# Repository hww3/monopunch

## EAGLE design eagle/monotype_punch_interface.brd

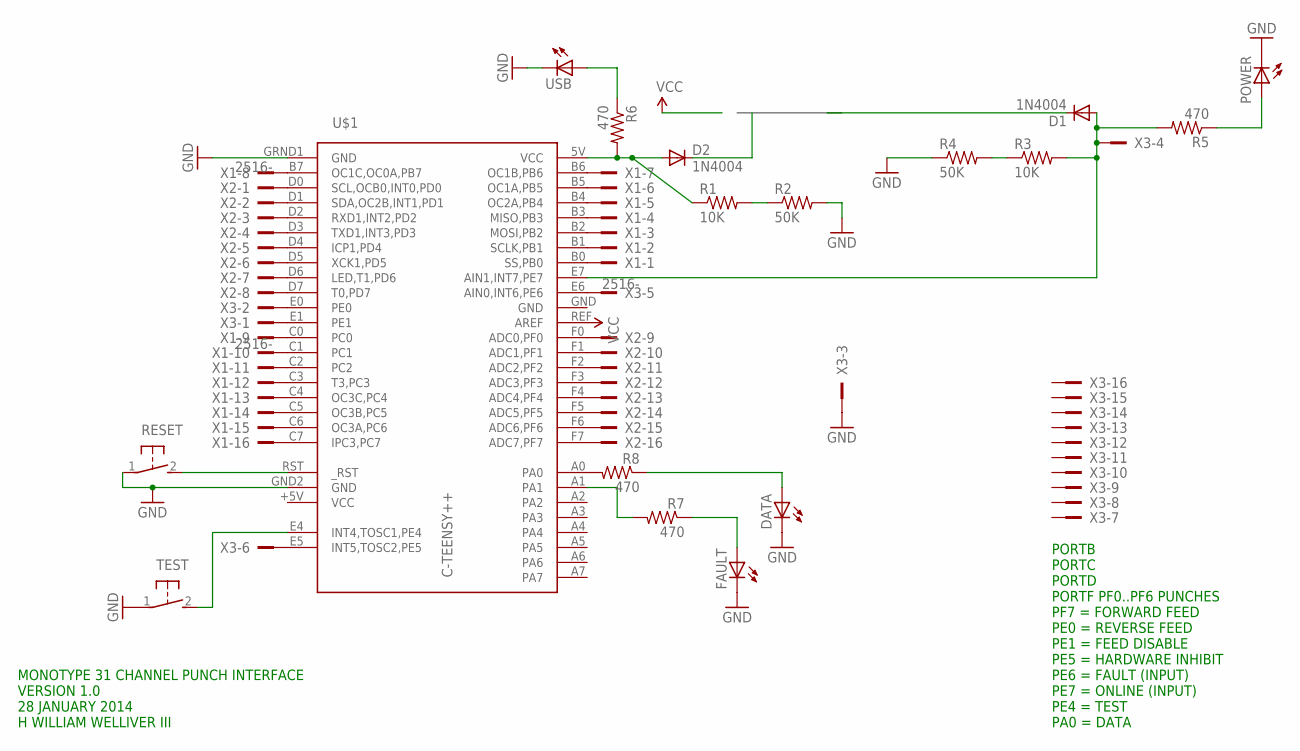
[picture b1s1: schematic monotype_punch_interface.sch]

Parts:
D1, D2: 1N4004; DO41-10
DATA: LED3MM
FAULT: LED3MM
POWER: LED3MM
R1, R3: 10K; AXIAL-0.4
R2, R4: 50K; AXIAL-0.4
R5, R6, R7, R8: 470; AXIAL-0.4
RESET: EVQPF
TEST: EVQPF
U$1: C-TEENSY++; TEENSY++
USB: LED3MM
X1, X2, X3: 2516-; PAK100/2500-16

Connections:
GND: DATA.K (C), FAULT.K (C), POWER.K (C), R2.P$2 (2), R4.P$1 (1), RESET.1, TEST.1, U$1.GND, U$1.GND2 (GND), U$1.GRND1 (GND), USB.K (C), X3.3
unnamed: RESET.2 (S), U$1.RST (_RST)
unnamed: TEST.2 (S), U$1.E4 (INT4,TOSC1,PE4)
unnamed: DATA.A, R8.P$1 (1)
unnamed: FAULT.A, R7.P$1 (1)
unnamed: R6.P$1 (1), USB.A
unnamed: POWER.A, R5.P$1 (1)
unnamed: D1.A, R3.P$2 (2), R5.P$2 (2), U$1.E7 (AIN1,INT7,PE7), X3.4
unnamed: R3.P$1 (1), R4.P$2 (2)
unnamed: R1.P$2 (2), R2.P$1 (1)
unnamed: U$1.B0 (SS,PB0), X1.1
unnamed: U$1.B1 (SCLK,PB1), X1.2
unnamed: U$1.B2 (MOSI,PB2), X1.3
unnamed: U$1.B3 (MISO,PB3), X1.4
unnamed: U$1.B4 (OC2A,PB4), X1.5
unnamed: U$1.B5 (OC1A,PB5), X1.6
unnamed: U$1.B6 (OC1B,PB6), X1.7
unnamed: U$1.B7 (OC1C,OC0A,PB7), X1.8
unnamed: U$1.C0, X1.9
unnamed: U$1.C1, X1.10
unnamed: U$1.C2, X1.11
unnamed: U$1.C3 (T3,PC3), X1.12
unnamed: U$1.C4 (OC3C,PC4), X1.13
unnamed: U$1.C5 (OC3B,PC5), X1.14
unnamed: U$1.C6 (OC3A,PC6), X1.15
unnamed: U$1.C7 (IPC3,PC7), X1.16
unnamed: U$1.D0 (SCL,OCB0,INT0,PD0), X2.1
unnamed: U$1.D1 (SDA,OC2B,INT1,PD1), X2.2
unnamed: U$1.D2 (RXD1,INT2,PD2), X2.3
unnamed: U$1.D3 (TXD1,INT3,PD3), X2.4
unnamed: U$1.D4 (ICP1,PD4), X2.5
unnamed: U$1.D5 (XCK1,PD5), X2.6
unnamed: U$1.D6 (LED,T1,PD6), X2.7
unnamed: U$1.D7 (T0,PD7), X2.8
unnamed: U$1.F0 (ADC0,PF0), X2.9
unnamed: U$1.F1 (ADC1,PF1), X2.10
unnamed: U$1.F2 (ADC2,PF2), X2.11
unnamed: U$1.F3 (ADC3,PF3), X2.12
unnamed: U$1.F4 (ADC4,PF4), X2.13
unnamed: U$1.F5 (ADC5,PF5), X2.14
unnamed: U$1.F6 (ADC6,PF6), X2.15
unnamed: U$1.F7 (ADC7,PF7), X2.16
unnamed: U$1.E1, X3.1
unnamed: U$1.E0, X3.2
unnamed: U$1.E6 (AIN0,INT6,PE6), X3.5
unnamed: U$1.E5 (INT5,TOSC2,PE5), X3.6
unnamed: R8.P$2 (2), U$1.A0
unnamed: R7.P$2 (2), U$1.A1
V2: D1.C, D2.A, D2.C, R1.P$1 (1), R6.P$2 (2), U$1.5V (VCC), U$1.+5V (VCC), U$1.REF (AREF)

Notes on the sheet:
MONOTYPE 31 CHANNEL PUNCH INTERFACE VERSION 1.0 28 JANUARY 2014 H WILLIAM WELLIVER III
PORTB PORTC PORTD PORTF PF0..PF6 PUNCHES PF7 = FORWARD FEED PE0 = REVERSE FEED PE1 = FEED DISABLE PE5 = HARDWARE INHIBIT PE6 = FAULT (INPUT) PE7 = ONLINE (INPUT) PE4 = TEST PA0 = DATA

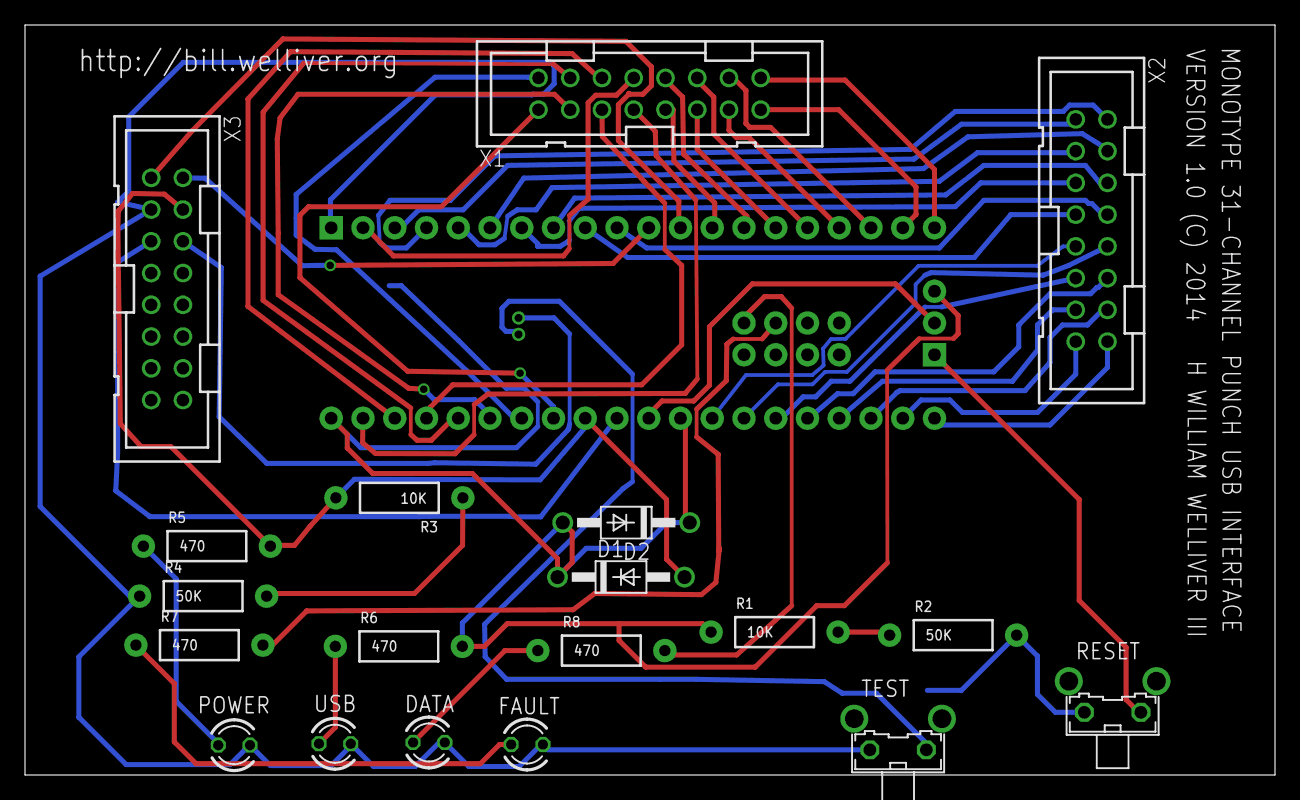
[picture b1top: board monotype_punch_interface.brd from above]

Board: 2 copper layers, 100.0 x 60.0 mm, 20 parts (1 on the bottom side), 49 nets.

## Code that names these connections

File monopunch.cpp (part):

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 * PORTB
 * PORTC
 * PORTD
 * PORTF PF0..PF6 PUNCHES
 * PF7 = FORWARD FEED
 * PE0 = REVERSE FEED
 * PE1 = FEED DISABLE
 * PE5 = HARDWARE INHIBIT
 * PE6 = FAULT (INPUT)
 * PE7 = ONLINE (INPUT)
 * PE4 = TEST (INPUT)
 * PA4 = DATA LED (OUTPUT)
 * PA5 = FAULT LED (OUTPUT)
 */

#define READONLINE() (PINE & _BV(PE7))
#define READFAULT() (PINE & _BV(PE6))
#define READTEST() (!(PINE & _BV(PE4)))
#define READDATA() (PINA & _BV(PA4))

#define FAULT(X) (X?(PORTA |= (1<<PA5)):(PORTA &= ~(1<<PA5)))
#define DATA(X) (X?(PORTA |= (1<<PA4)):(PORTA &= ~(1<<PA4)))
#define ONLINE(X) (X?(PORTE |= (1<<PE5)):(PORTE &= ~(1<<PE5)))

//TimerOne * Timer;

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	PORTD = 0;
	PORTE = 0;
	PORTF = 0;
	PORTE|=(1<<PE1);

	DDRB = 0xff;
	DDRC = 0xff;
	DDRD = 0xff;
	DDRF = 0xff;

	DDRE |= (1<<PE0); // OUTPUT
	DDRE |= (1<<PE1); // OUTPUT
	DDRE |= (1<<PE5); // OUTPUT

	PORTE |= (1<<PE4);
	PORTE &= ~(1<<PE6);
//	PORTE &= ~(1<<PE7);

	DDRA |= (1<<PA5); // OUTPUT
	DDRA |= (1<<PA4); // OUTPUT
	DDRA |= (1<<PA0); // OUTPUT


	DDRE &= ~(1<<PE6); // INPUT
	DDRE &= ~(1<<PE7); // INPUT
	DDRE &= ~(1<<PE4); // INPUT

	attachInterrupt(INT4, goTest, CHANGE);
	attachInterrupt(INT6, goFault, CHANGE);
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	PORTC = 0;
	PORTD = 0;
	PORTF = 0;
  PORTE |= (1<<PE0);
	delay(6);

  PORTE &= ~(1<<PE0);
}

void beginPunch()
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	PORTD = code[1];
	PORTF = (code[0]);

//	PORTF |= (1<<PF7); // leave the high pin on, for paper feed.

	delay(3);

	PORTB = 0;
	PORTC = 0;
	PORTD = 0;
	PORTF &= (1<<PF7); // leave the high pin on, for paper feed.

	delay(3);

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 // delay(1000);
//	return;
//	PORTE = 0;
//  PORTE |=(1<<PE1);
/*
	PORTF=0;
	PORTE|=(1<<PE1);
	//PORTF|=(1<<PF7);
	delay(6);
	//PORTF=0;
	PORTE&=~(1<<PE1);
	delay(1000);
	return;
	*/
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
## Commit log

2013-12-08 initial set of firmware for 31 channel punch.
2014-02-15 add notes for additional pins.
2014-02-24 functionally complete version, basically.
2014-03-11 updates for final hw prototype.
2014-05-11 release 1.0
2014-05-11 version
2014-05-11 Added tag v1.0.0 for changeset 07e051bc0239
2014-05-13 works with rib.pike again.
2014-05-13 Added tag v1.0.1 for changeset c4ea340d6f54
2014-05-13 adding eagle stuff (outdated, due to greenwires on the board.)
2014-05-20 update to 1.0.2: fix test pattern and command mode after test.
2014-05-26 v1.0.3; deals with the test button better when offline.
    --HG--
    extra : rebase_source : 04dcff52e4c6466baf1a1342fe0a6335e298e250

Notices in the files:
eagle/monotype_punch_interface.brd:
VERSION 1.0 (C) 2014
parts and their libraries:
SparkFun: Licensing: CC v3.0 Share-Alike You are welcome to use this library for commercial purposes.
